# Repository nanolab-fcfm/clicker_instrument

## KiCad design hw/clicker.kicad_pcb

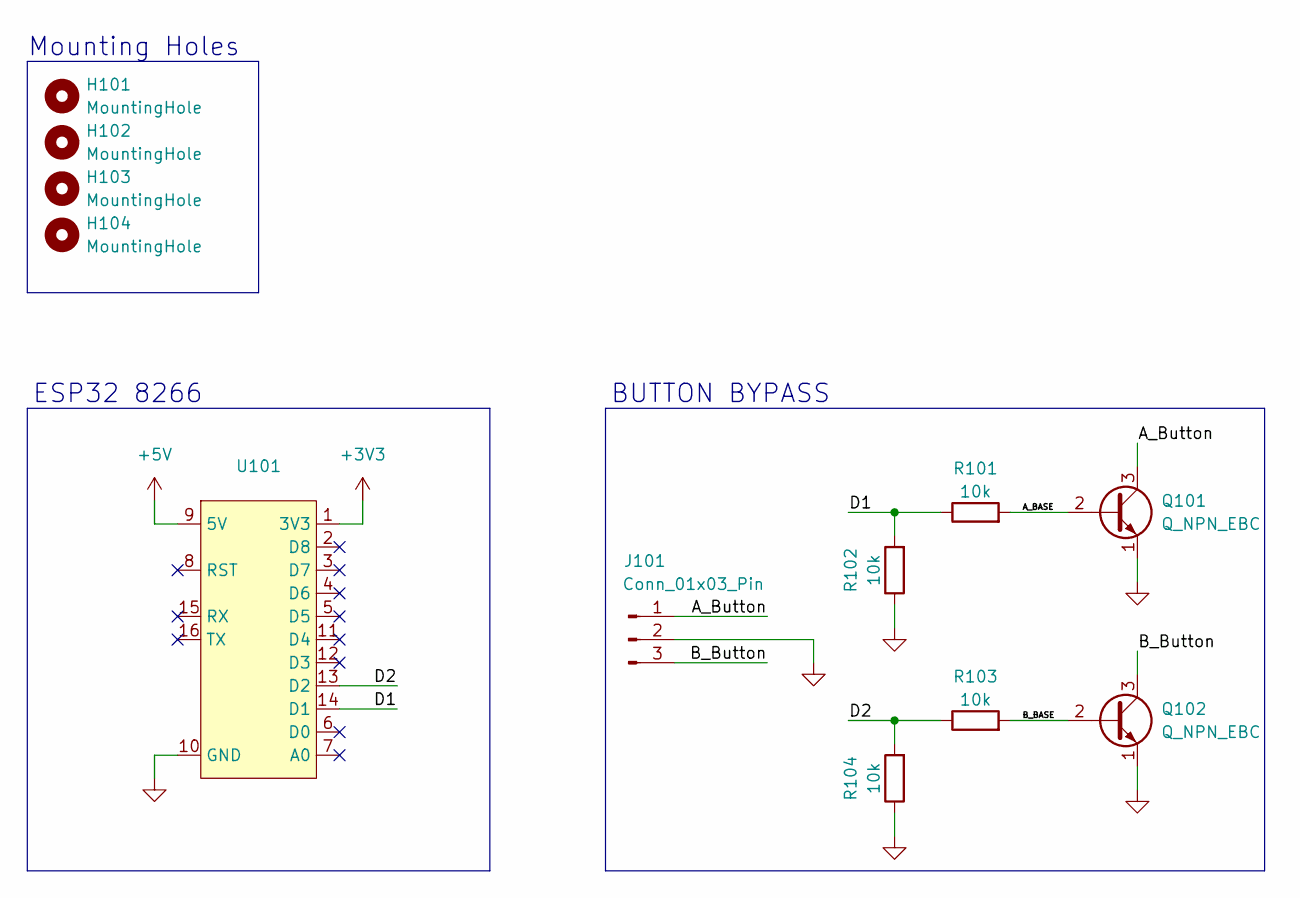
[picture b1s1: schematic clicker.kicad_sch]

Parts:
H101, H102, H103, H104: MountingHole; MountingHole_2.5mm
J101: Conn_01x03_Pin; PinHeader_1x03_P2.54mm_Vertical
Q101, Q102: Q_NPN_EBC; TO-92L_HandSolder
R101, R102, R103, R104: 10k; R_Axial_DIN0204_L3.6mm_D1.6mm_P7.62mm_Horizontal
U101: ESP

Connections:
+3V3: U101.1 (3V3)
+5V: U101.9 (5V)
/A_BASE: Q101.2 (B), R101.2
/A_Button: J101.1, Q101.3 (C)
/B_BASE: Q102.2 (B), R103.2
/B_Button: J101.3, Q102.3 (C)
/D1: R101.1, R102.2, U101.14 (D1)
/D2: R103.1, R104.2, U101.13 (D2)
GND: J101.2, Q101.1 (E), Q102.1 (E), R102.1, R104.1, U101.10 (GND)

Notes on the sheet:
Mounting Holes
BUTTON BYPASS
ESP32 8266

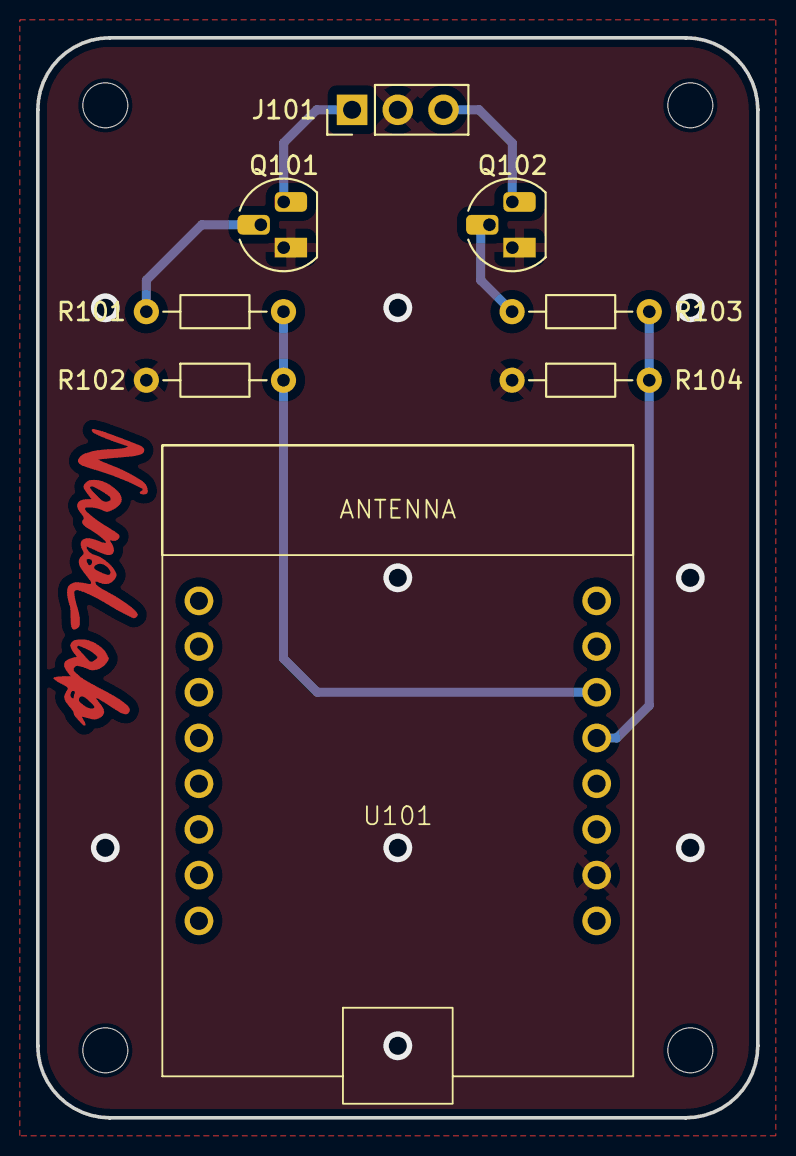
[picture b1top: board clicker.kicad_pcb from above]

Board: 2 copper layers, 40.0 x 60.0 mm, 12 parts (0 on the bottom side), 7 nets.

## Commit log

2025-02-17 firmware
2025-02-17 README
2025-02-17 Calling AB command 2 times instead of 3 in the reachTargetTemperature function
2025-02-17 Code updated to work with python
2025-02-19 Update clicker.ino to include IDN
2025-02-19 Fix extra "{" in main.ino
2025-05-26 clicker hw
2025-05-26 gitignore for KiCAD files
2026-06-20 Add MkDocs documentation site
    Add a NanoLab-branded MkDocs Material documentation site (Overview, Hardware,
    Firmware, Usage) deployable to GitHub Pages at nanolab.cl/clicker_instrument/, consistent with
    the other NanoLab project docs. Includes the Pages deploy workflow and shared
    branding (logo, palette, footer, back-to-NanoLab link).
2026-06-21 Point back-link to the NanoLab documentation hub
    Change the '⬅ NanoLab' nav link to target nanolab.cl/documentation/ (the docs
    hub) instead of the site root, for consistent cross-navigation.
2026-06-21 Add interactive 3D PCB model to the hardware docs
    Export the KiCad board (with through-hole component 3D models) to GLB via
    kicad-cli and embed it with Google's <model-viewer> web component, so the
    Hardware page shows a rotate/zoom/pan 3D render of the PCB. Includes a documented
    Docker one-liner to regenerate the model after board changes.
2026-06-21 Fix 3D model: colour components and use a dark viewer background
    KiCad's GLB export omits component materials, so components rendered solid white
    on a light background. Add tools/recolor_glb.py to assign materials to the
    component meshes by reference designator (blue resistors, black transistors and
    header), regenerate the GLB, and give <model-viewer> a dark background with
    neutral tone-mapping so the board and parts read clearly.
